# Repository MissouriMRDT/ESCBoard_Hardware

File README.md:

# MotorController_Hardware
New motor controllers developed for 2022 competition
Based on VESC 4.12 Motor Controllers

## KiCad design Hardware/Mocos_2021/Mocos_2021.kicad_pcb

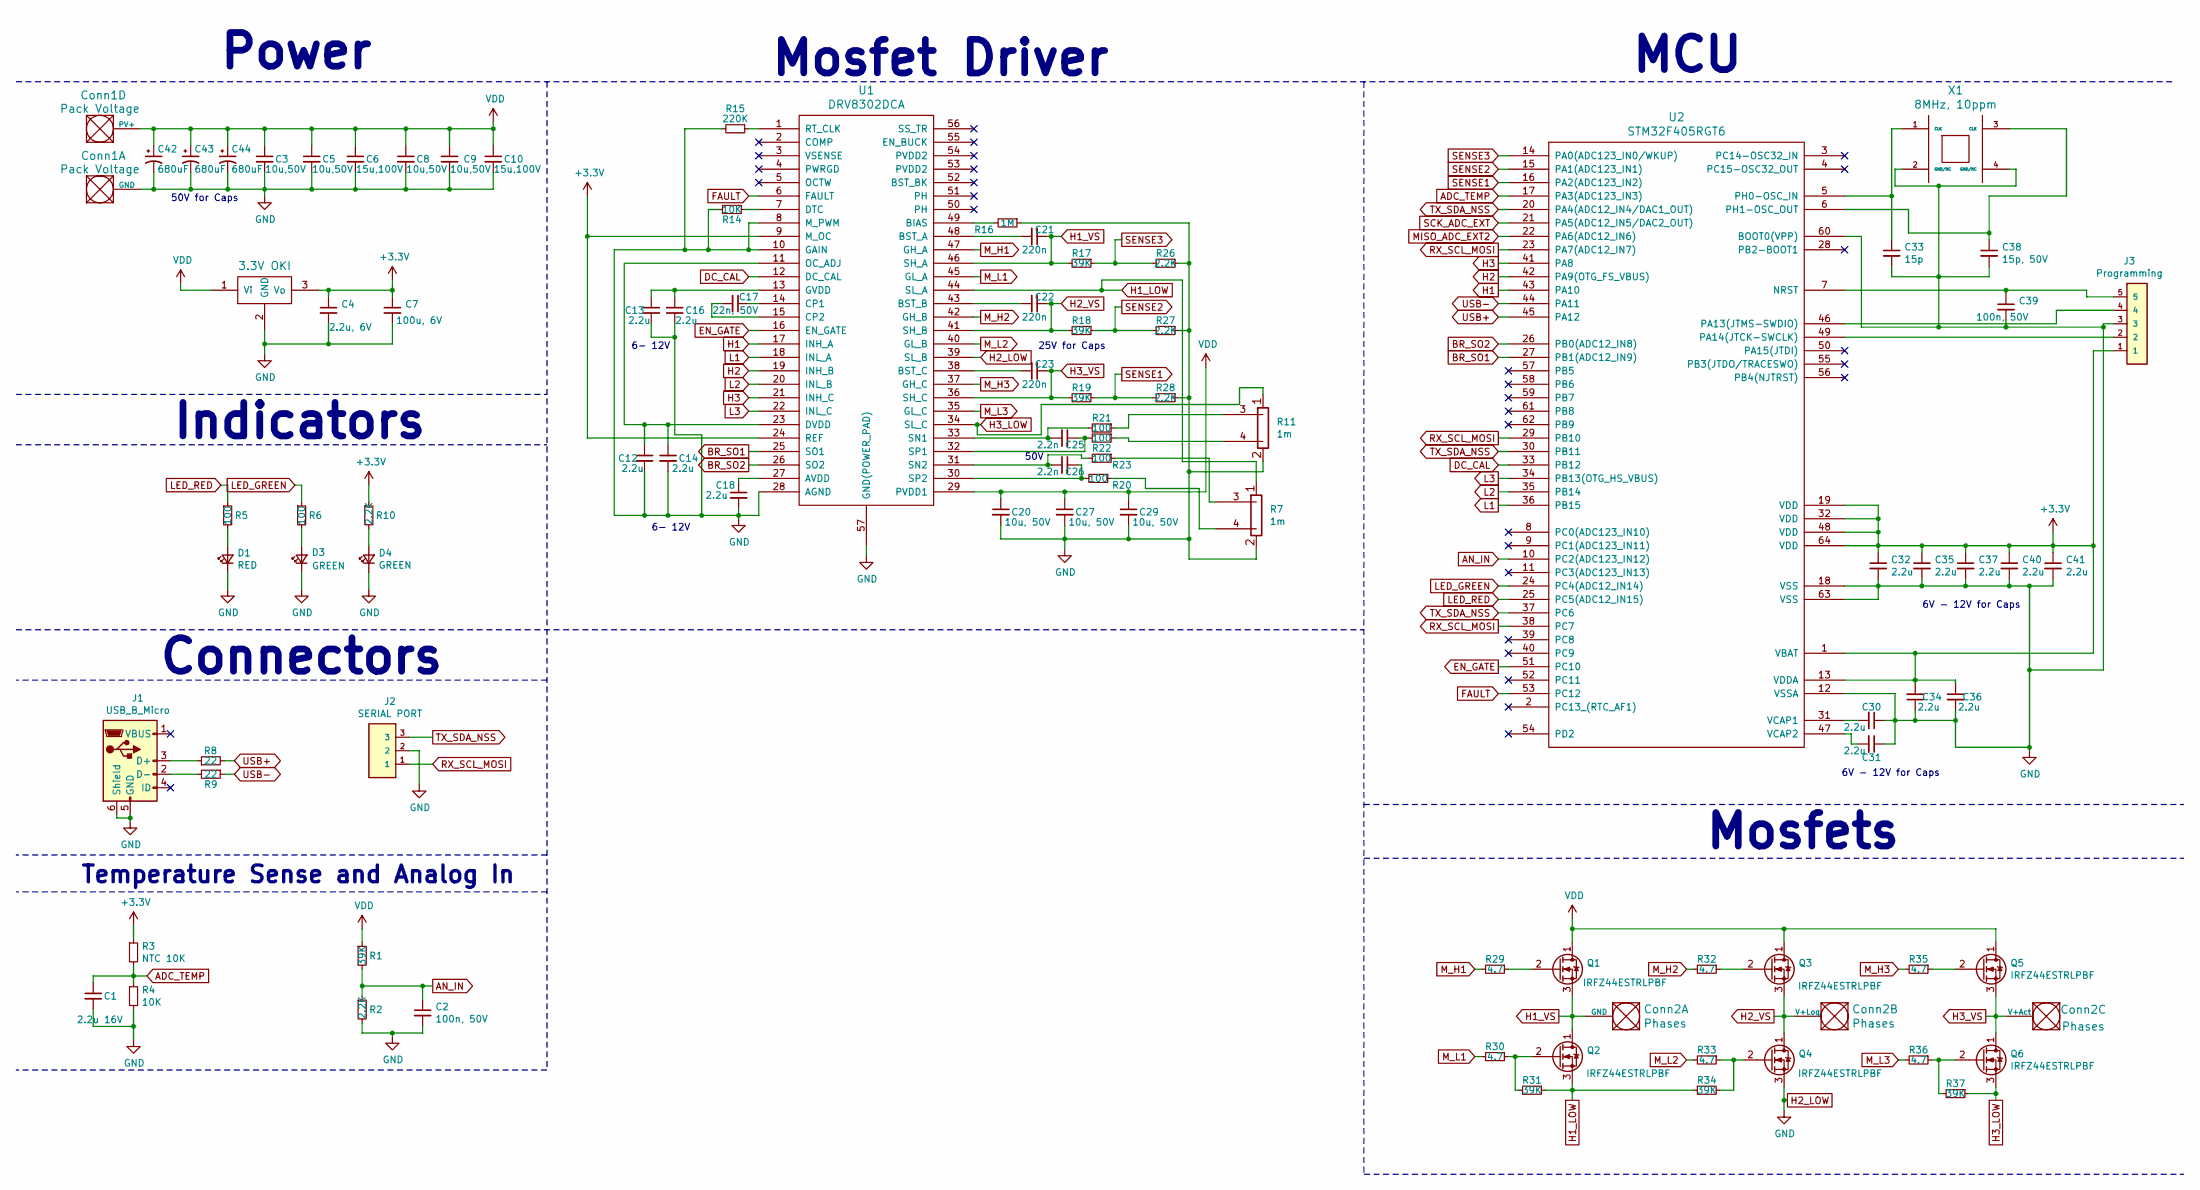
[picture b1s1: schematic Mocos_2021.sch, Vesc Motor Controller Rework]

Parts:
C1: 2.2u 16V; C_0402_1005Metric_Pad0.74x0.62mm_HandSolder
C2, C39: 100n, 50V; C_0603_1608Metric_Pad1.08x0.95mm_HandSolder
C3, C5, C8, C9: 10u,50V; C_1210_3225Metric_Pad1.33x2.70mm_HandSolder
C4: 2.2u, 6V; C_0402_1005Metric_Pad0.74x0.62mm_HandSolder
C6, C10: 15u,100V; C_2220_5650Metric_Pad1.97x5.40mm_HandSolder
C7: 100u, 6V; C_0805_2012Metric_Pad1.18x1.45mm_HandSolder
C12, C13, C14, C16, C18, C30, C31, C32, C34, C35, C36, C37, C40, C41: 2.2u; C_0402_1005Metric_Pad0.74x0.62mm_HandSolder
C17: 22n, 50V; C_0402_1005Metric_Pad0.74x0.62mm_HandSolder
C20, C27, C29: 10u, 50V; C_1210_3225Metric_Pad1.33x2.70mm_HandSolder
C21, C22, C23: 220n; C_0805_2012Metric_Pad1.18x1.45mm_HandSolder
C25, C26: 2.2n; C_0402_1005Metric_Pad0.74x0.62mm_HandSolder
C33: 15p; C_0603_1608Metric_Pad1.08x0.95mm_HandSolder
C38: 15p, 50V; C_0603_1608Metric_Pad1.08x0.95mm_HandSolder
C42, C43, C44: 680uF; CP_Radial_D16.0mm_P7.50mm
Conn1: Pack Voltage; Anderson_2_Horizontal_Side_by_Side_PV
Conn2: Phases; Anderson_3_Horizontal_Side_by_Side
D1: RED; LED_0603_1608Metric_Pad1.05x0.95mm_HandSolder
D3, D4: GREEN; LED_0603_1608Metric_Pad1.05x0.95mm_HandSolder
J1: USB_B_Micro; MOLEX_47346-0001
J2: SERIAL PORT; MOLEX_uF_S_03_Horizontal
J3: Programming; MOLEX_uF_S_05_Horizontal
Q1, Q2, Q3, Q4, Q5, Q6: IRFZ44ESTRLPBF
R1, R17, R18, R19, R31, R34, R37: 39K; R_0603_1608Metric_Pad0.98x0.95mm_HandSolder
R2, R10, R26, R27, R28: 2.2K; R_0603_1608Metric_Pad0.98x0.95mm_HandSolder
R3: NTC 10K; R_0603_1608Metric_Pad0.98x0.95mm_HandSolder
R4, R14: 10K; R_0603_1608Metric_Pad0.98x0.95mm_HandSolder
R5, R6, R20, R21, R22, R23: 100; R_0603_1608Metric_Pad0.98x0.95mm_HandSolder
R7, R11: 1m; WSLP2726
R8, R9: 22; R_0603_1608Metric_Pad0.98x0.95mm_HandSolder
R15: 220K; R_0603_1608Metric_Pad0.98x0.95mm_HandSolder
R16: 1M; R_0603_1608Metric_Pad0.98x0.95mm_HandSolder
R29, R30, R32, R33, R35, R36: 4.7; R_0603_1608Metric_Pad0.98x0.95mm_HandSolder
U1: DRV8302DCA; TSSOP-56-PP
U2: STM32F405RGT6; lqfp64_pad_mod
U3: 3.3V OKI; OKI_Horizontal
X1: 8MHz, 10ppm; Crystal_5x3mm

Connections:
+3V3: C4.1, C7.1, C32.1, C34.2, C35.1, C36.1, C37.1, C40.1, C41.1, J3.1, R3.1, R10.1, U1.9 (M_OC), U1.24 (REF), U2.1 (VBAT), U2.13 (VDDA), U2.19 (VDD), U2.32 (VDD), U2.48 (VDD), U2.64 (VDD), U3.3 (Vo)
ADC_TEMP: C1.1, R3.2, R4.1, U2.17 (PA3(ADC123_IN3))
AN_IN: C2.1, R1.2, R2.1, U2.10 (PC2(ADC123_IN12))
BR_SO1: U1.25 (SO1), U2.27 (PB1(ADC12_IN9))
BR_SO2: U1.26 (SO2), U2.26 (PB0(ADC12_IN8))
DC_CAL: U1.12 (DC_CAL), U2.33 (PB12)
EN_GATE: U1.16 (EN_GATE), U2.51 (PC10)
FAULT: U1.6 (FAULT), U2.53 (PC12)
H1: U1.17 (INH_A), U2.43 (PA10)
H1_LOW: Q2.3 (S), R7.1, R31.1, R34.1, U1.44 (SL_A)
H1_VS: C21.1, Conn2.1 (GND), Q1.3 (S), Q2.1 (D), R17.2, U1.46 (SH_A)
H2: U1.19 (INH_B), U2.42 (PA9(OTG_FS_VBUS))
H2_LOW: C1.2, C2.2, C3.2, C4.2, C5.2, C6.2, C7.2, C8.2, C9.2, C10.2, C12.2, C13.2, C14.2, C16.2, C18.2, C20.2, C27.2, C29.2, C30.1, C31.1, C32.2, C33.2, C34.1, C35.2, C36.2, C37.2, C38.2, C39.2, C40.2, C41.2, C42.2, C43.2, C44.2, Conn1.1 (GND), D1.1 (K), D3.1 (K), D4.1 (K), J1.5 (GND), J1.6 (Shield), J2.2, J3.3, Q4.3 (S), R2.2, R4.2, R7.2, R11.2, R14.2, R15.2, R16.1, R26.1, R27.1, R28.1, U1.8 (M_PWM), U1.10 (GAIN), U1.28 (AGND), U1.39 (SL_B), U1.57 (GND(POWER_PAD)), U2.12 (VSSA), U2.18 (VSS), U2.60 (BOOT0(VPP)), U2.63 (VSS), U3.2 (GND), X1.2 (GND/NC), X1.4 (GND/NC)
H2_VS: C22.1, Conn2.2 (V+Log), Q3.3 (S), Q4.1 (D), R18.2, U1.41 (SH_B)
H3: U1.21 (INH_C), U2.41 (PA8)
H3_LOW: Q6.3 (S), R11.1, R37.1, U1.34 (SL_C)
H3_VS: C23.1, Conn2.3 (V+Act), Q5.3 (S), Q6.1 (D), R19.2, U1.36 (SH_C)
L1: U1.18 (INL_A), U2.36 (PB15)
L2: U1.20 (INL_B), U2.35 (PB14)
L3: U1.22 (INL_C), U2.34 (PB13(OTG_HS_VBUS))
LED_GREEN: R6.1, U2.24 (PC4(ADC12_IN14))
LED_RED: R5.1, U2.25 (PC5(ADC12_IN15))
M_H1: R29.2, U1.47 (GH_A)
M_H2: R32.2, U1.42 (GH_B)
M_H3: R35.2, U1.37 (GH_C)
M_L1: R30.2, U1.45 (GL_A)
M_L2: R33.2, U1.40 (GL_B)
M_L3: R36.2, U1.35 (GL_C)
unnamed: C12.1, C14.1, U1.11 (OC_ADJ), U1.23 (DVDD)
unnamed: C13.1, C16.1, U1.13 (GVDD)
unnamed: C17.1, U1.14 (CP1)
unnamed: C17.2, U1.15 (CP2)
unnamed: C18.1, U1.27 (AVDD)
unnamed: C21.2, U1.48 (BST_A)
unnamed: C22.2, U1.43 (BST_B)
unnamed: C23.2, U1.38 (BST_C)
unnamed: C25.1, R22.2, U1.32 (SP1)
unnamed: C25.2, R21.2, U1.33 (SN1)
unnamed: C26.1, R20.2, U1.30 (SP2)
unnamed: C26.2, R23.2, U1.31 (SN2)
unnamed: C30.2, U2.31 (VCAP1)
unnamed: C31.2, U2.47 (VCAP2)
unnamed: C33.1, U2.5 (PH0-OSC_IN), X1.1 (CLK)
unnamed: C38.1, U2.6 (PH1-OSC_OUT), X1.3 (CLK)
unnamed: C39.1, J3.5, U2.7 (NRST)
unnamed: D1.2 (A), R5.2
unnamed: D3.2 (A), R6.2
unnamed: D4.2 (A), R10.2
unnamed: J1.2 (D-), R9.2
unnamed: J1.3 (D+), R8.1
unnamed: J3.2, U2.49 (PA14(JTCK-SWCLK))
unnamed: J3.4, U2.46 (PA13(JTMS-SWDIO))
unnamed: Q1.2 (G), R29.1
unnamed: Q2.2 (G), R30.1, R31.2
unnamed: Q3.2 (G), R32.1
unnamed: Q4.2 (G), R33.1, R34.2
unnamed: Q5.2 (G), R35.1
unnamed: Q6.2 (G), R36.1, R37.2
unnamed: R11.3, R21.1
unnamed: R11.4, R22.1
unnamed: R14.1, U1.7 (DTC)
unnamed: R15.1, U1.1 (RT_CLK)
unnamed: R16.2, U1.49 (BIAS)
unnamed: R7.4, R20.1
unnamed: R7.3, R23.1
RX_SCL_MOSI: J2.1, U2.23 (PA7(ADC12_IN7)), U2.29 (PB10), U2.38 (PC7)
SENSE1: R19.1, R28.2, U2.16 (PA2(ADC123_IN2))
SENSE2: R18.1, R27.2, U2.15 (PA1(ADC123_IN1))
SENSE3: R17.1, R26.2, U2.14 (PA0(ADC123_IN0/WKUP))
TX_SDA_NSS: J2.3, U2.20 (PA4(ADC12_IN4/DAC1_OUT)), U2.30 (PB11), U2.37 (PC6)
USB+: R8.2, U2.45 (PA12)
USB-: R9.1, U2.44 (PA11)
VDD: C3.1, C5.1, C6.1, C8.1, C9.1, C10.1, C20.1, C27.1, C29.1, C42.1, C43.1, C44.1, Conn1.4 (PV+), Q1.1 (D), Q3.1 (D), Q5.1 (D), R1.1, U1.29 (PVDD1), U3.1 (Vi)

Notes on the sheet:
50V for Caps
6V - 12V for Caps
6- 12V
25V for Caps
50V
Power
Mosfet Driver
MCU
Mosfets
Indicators
Connectors
Temperature Sense and Analog In

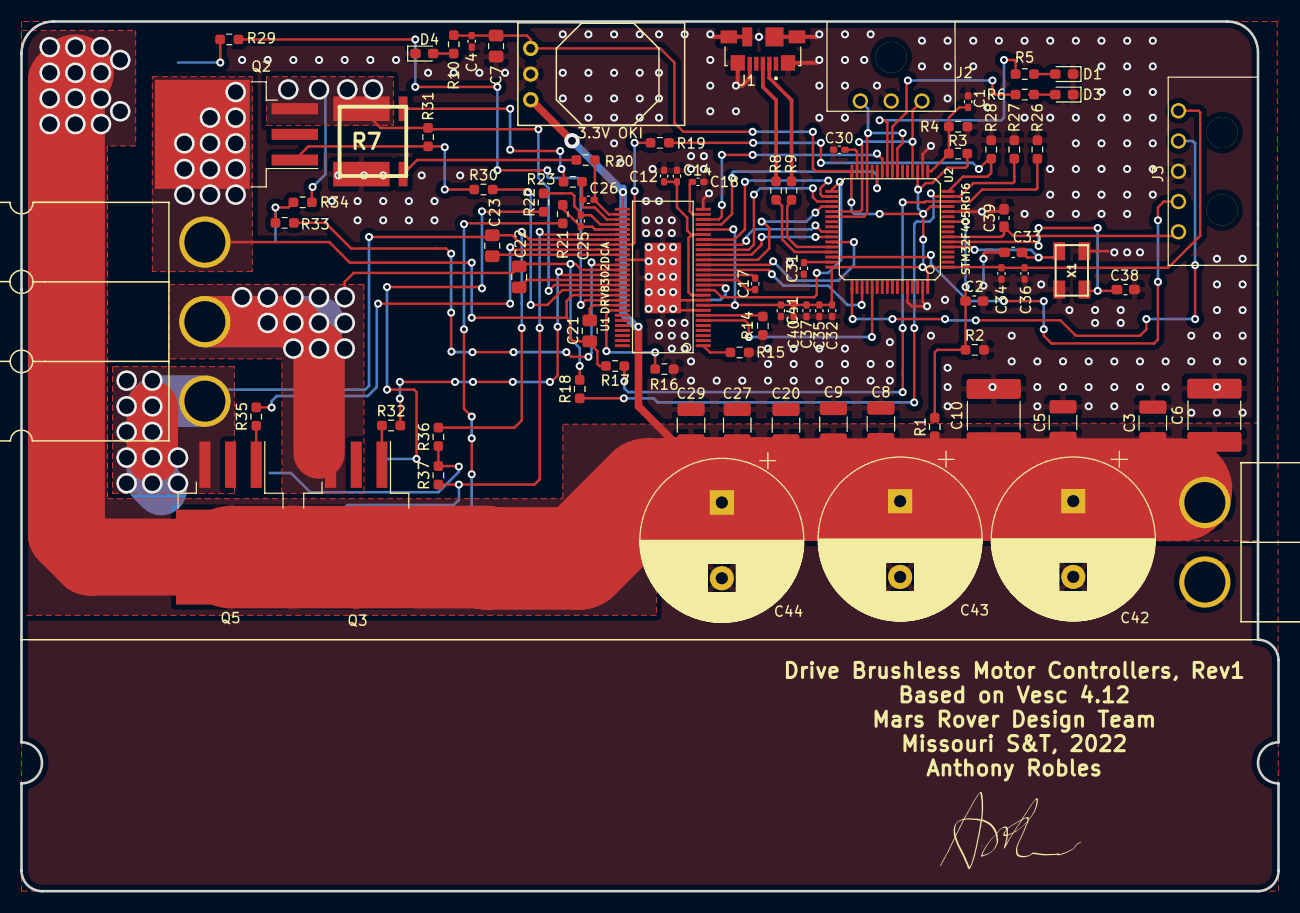
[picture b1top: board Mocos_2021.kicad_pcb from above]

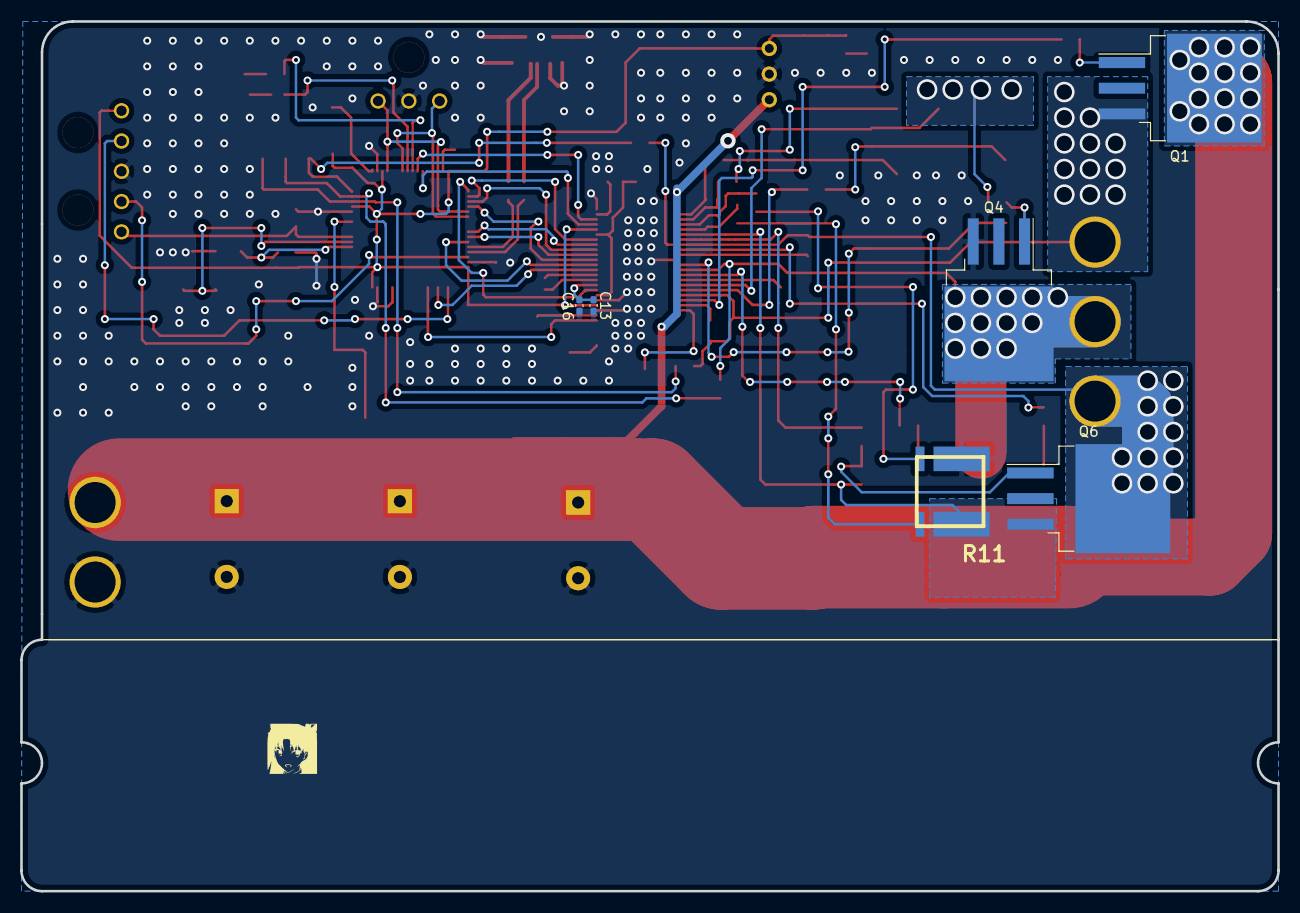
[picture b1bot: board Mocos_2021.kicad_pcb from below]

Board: 2 copper layers, 124.5 x 86.1 mm, 90 parts (6 on the bottom side), 73 nets.

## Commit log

2020-09-11 created project
2020-10-09 Added Libraries, Began Microcontroller sheet
2020-10-12 finished schematic
2021-03-19 Added Rev4.1 for reference
2021-08-18 Added Schematic and working on Layout
2021-08-19 Added footprints to board
2021-08-21 Finished STM32 Layout
2021-08-21 Added 3.3V Oki for cleaner layout
2021-08-24 Retraced the entire VDD Net and readjusted the Mosfet placement
2021-08-24 Moved Q6 to a better position for Routing
2021-08-24 Finished routing all but the sense resistors
2021-08-25 Finished layout and generated Gerbs
2021-08-28 Finished BOM and Fixed some Layout errors such as trace tolerance
